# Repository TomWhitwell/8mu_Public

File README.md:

### 8mu Public Repo

This is the public repo for the Music Thing Modular 8mu midi controller. 

[Documentation is here](https://www.musicthing.co.uk/8mu)

Currently this contains firmware for 8mu v1, devices bought before August 2026 that have a SAMD21 chip. 

Devices bought after August 2026 are v2. They have v2 clearly marked next to the USB socket, and have a RP2040 chip. 
 
The current production SAMD21 8mu v1 firmware source is in
[`Firmware_v1/8mu`](Firmware_v1/8mu). Release firmware can be downloaded from the
[Smith-Kakehashi releases page](https://github.com/TomWhitwell/Smith-Kakehashi/releases).

This repo also contains source for the [legacy 8mu editor](https://tomwhitwell.github.io/Smith-Kakehashi/), which has now been replaced by the [main 16n Editor for 16m | 16nx | 8mu](https://16n-faderbank.github.io/editor/). 

Firmware is MIT Licensed. 
Hardware is CC-BY-SA.

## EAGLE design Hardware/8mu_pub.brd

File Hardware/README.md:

Open hardware files coming soon

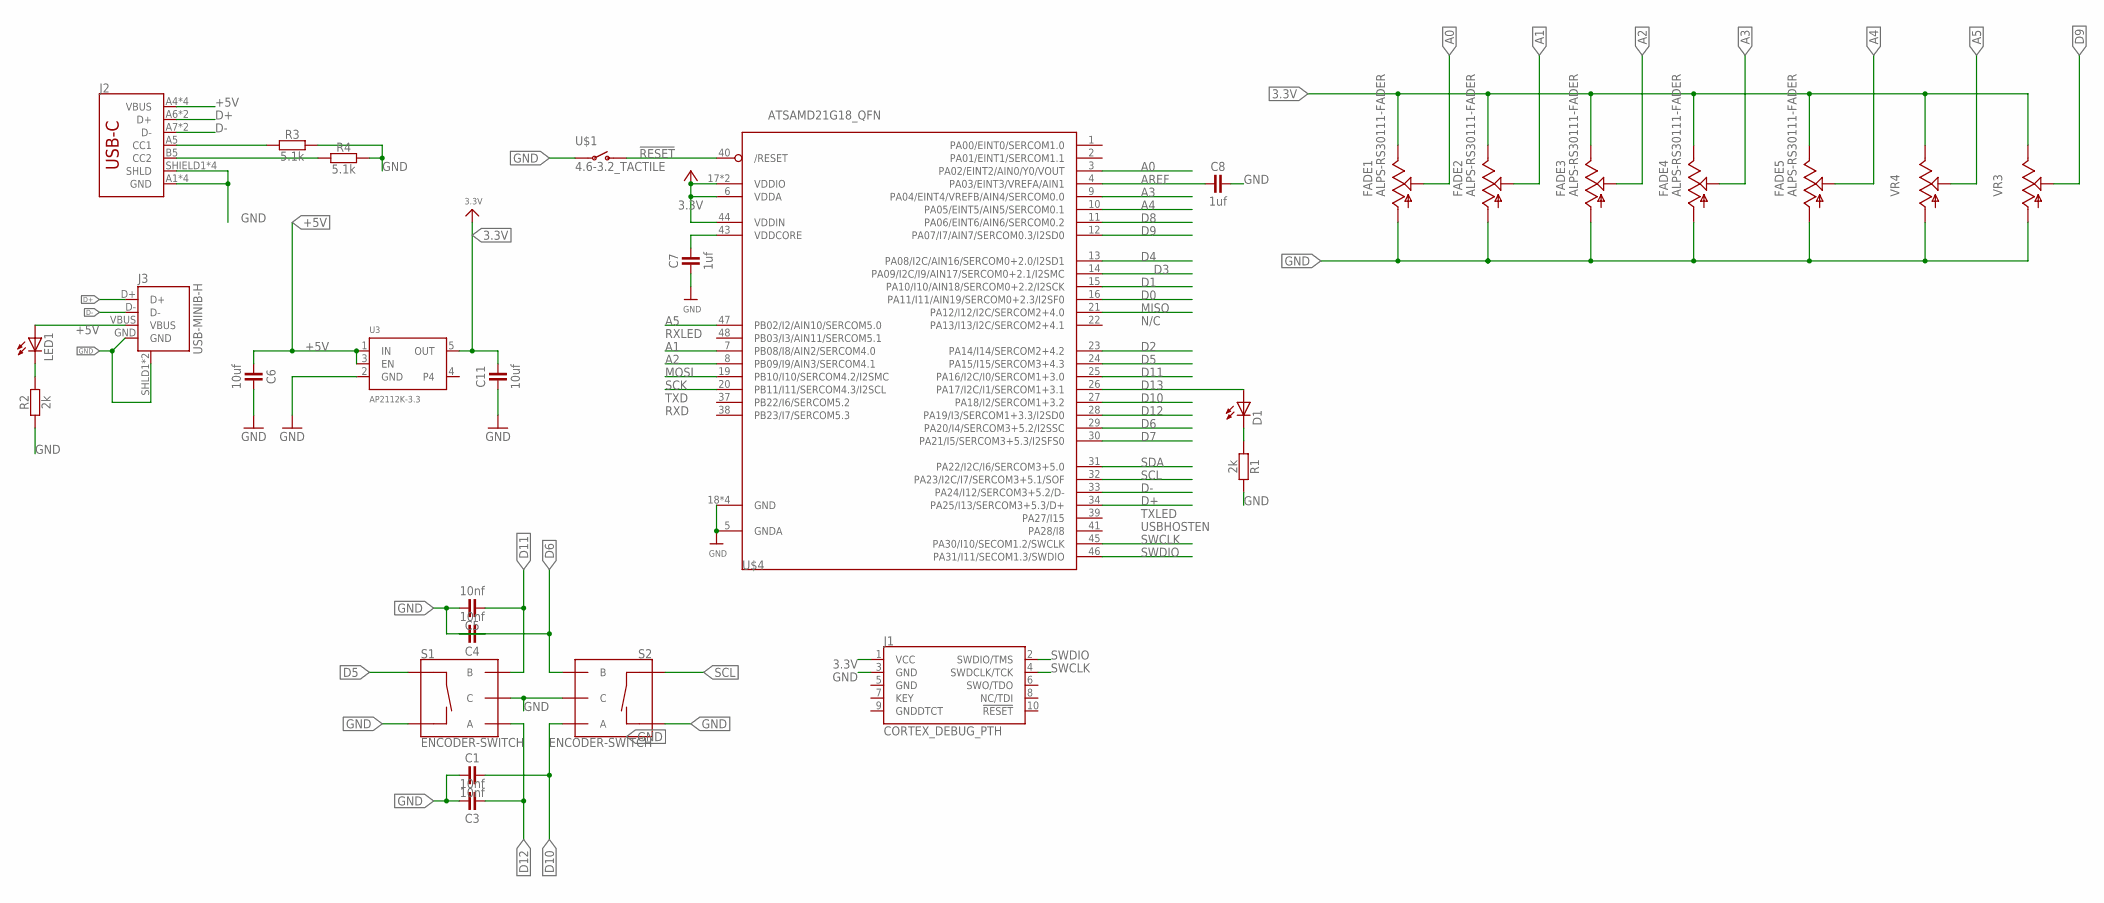
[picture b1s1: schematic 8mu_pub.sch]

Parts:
C1, C3, C4, C5: 10nf; C0603
C6, C11: 10uf; C0603
C7, C8: 1uf; C0603
D1: LED3MM
FADE1, FADE2, FADE3, FADE4, FADE5: ALPS-RS30111-FADER
J1: CORTEX_DEBUG_PTH; 2X5-PTH-1.27MM
J2: USB_C; CX90M-16P-USB-C-MIDMOUNT
J3: USB-MINIB-H
LED1: LED3MM
R1, R2: 2k; C0603
R3, R4: 5.1k; C0603
S1, S2: ENCODER-SWITCH; ROTARY_ENC_PLAIN
U3: AP2112K-3.3; SOT23-5
U$1: 4.6-3.2_TACTILE; TACTILE_SWITCH_SMD_4.6X2.8MM
U$4: ATSAMD21G18_QFN; TQFN48_7MM
VR3, VR4: 9MM_SNAP-IN_POT_; 9MM_SNAP-IN_POT

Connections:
3.3V: C11.2, FADE1.3 (E), FADE2.3 (E), FADE3.3 (E), FADE4.3 (E), FADE5.3 (E), J1.1 (VCC), U3.5 (OUT), U$4.6 (VDDA), U$4.17 (VDDIO), U$4.36 (VDDIO), U$4.44 (VDDIN), VR3.3 (E), VR4.3 (E)
!RESET: U$1.3 (O), U$1.4 (O), U$4.40 (/RESET)
+5V: C6.1, J2.A4 (VBUS), J2.A9 (VBUS), J2.B4 (VBUS), J2.B9 (VBUS), J3.VBUS, LED1.A, U3.1 (IN), U3.3 (EN)
A0: FADE1.2 (S), U$4.3 (PA02/EINT2/AIN0/Y0/VOUT)
A1: FADE2.2 (S), U$4.7 (PB08/I8/AIN2/SERCOM4.0)
A2: FADE3.2 (S), U$4.8 (PB09/I9/AIN3/SERCOM4.1)
A3: FADE4.2 (S), U$4.9 (PA04/EINT4/VREFB/AIN4/SERCOM0.0)
A4: FADE5.2 (S), U$4.10 (PA05/EINT5/AIN5/SERCOM0.1)
A5: U$4.47 (PB02/I2/AIN10/SERCOM5.0), VR4.2 (S)
AREF: C8.1, U$4.4 (PA03/EINT3/VREFA/AIN1)
D0: U$4.16 (PA11/I11/AIN19/SERCOM0+2.3/I2SF0)
D1: U$4.15 (PA10/I10/AIN18/SERCOM0+2.2/I2SCK)
D2: U$4.23 (PA14/I14/SERCOM2+4.2)
D3: U$4.14 (PA09/I2C/I9/AIN17/SERCOM0+2.1/I2SMC)
D4: U$4.13 (PA08/I2C/AIN16/SERCOM0+2.0/I2SD1)
D5: S1.SW+, U$4.24 (PA15/I15/SERCOM3+4.3)
D6: C4.2, S2.B, U$4.29 (PA20/I4/SERCOM3+5.2/I2SSC)
D7: U$4.30 (PA21/I5/SERCOM3+5.3/I2SFS0)
D8: U$4.11 (PA06/EINT6/AIN6/SERCOM0.2)
D9: U$4.12 (PA07/I7/AIN7/SERCOM0.3/I2SD0), VR3.2 (S)
D10: C1.2, S2.A, U$4.27 (PA18/I2/SERCOM1+3.2)
D11: C5.1, S1.B, U$4.25 (PA16/I2C/I0/SERCOM1+3.0)
D12: C3.1, S1.A, U$4.28 (PA19/I3/SERCOM1+3.3/I2SD0)
D13: D1.A, U$4.26 (PA17/I2C/I1/SERCOM1+3.1)
D+: J2.A6 (D+), J2.B6 (D+), J3.D+, U$4.34 (PA25/I13/SERCOM3+5.3/D+)
D-: J2.A7 (D-), J2.B7 (D-), J3.D-, U$4.33 (PA24/I12/SERCOM3+5.2/D-)
GND: C1.1, C3.2, C4.1, C5.2, C6.2, C7.1, C8.2, C11.1, FADE1.1 (A), FADE2.1 (A), FADE3.1 (A), FADE4.1 (A), FADE5.1 (A), J1.3 (GND), J2.A1 (GND), J2.A12 (GND), J2.B1 (GND), J2.B12 (GND), J2.SHIELD1 (SHLD), J2.SHIELD2 (SHLD), J2.SHIELD3 (SHLD), J2.SHIELD4 (SHLD), J3.GND, J3.SHLD1 (SHIELD), J3.SHLD2 (SHIELD), R1.2, R2.1, R3.2, R4.2, S1.C, S1.SW-, S2.C, S2.SW-, U3.2 (GND), U$1.1, U$1.2, U$4.5 (GNDA), U$4.18 (GND), U$4.35 (GND), U$4.42 (GND), U$4.THERMAL (GND), VR3.1 (A), VR4.1 (A)
MISO: U$4.21 (PA12/I12/I2C/SERCOM2+4.0)
MOSI: U$4.19 (PB10/I10/SERCOM4.2/I2SMC)
unnamed: D1.K (C), R1.1
unnamed: LED1.K (C), R2.2
unnamed: J2.A5 (CC1), R3.1
unnamed: J2.B5 (CC2), R4.1
SCK: U$4.20 (PB11/I11/SERCOM4.3/I2SCL)
SCL: S2.SW+, U$4.32 (PA23/I2C/I7/SERCOM3+5.1/SOF)
SDA: U$4.31 (PA22/I2C/I6/SERCOM3+5.0)
SWCLK: J1.4 (SWDCLK/TCK), U$4.45 (PA30/I10/SECOM1.2/SWCLK)
SWDIO: J1.2 (SWDIO/TMS), U$4.46 (PA31/I11/SECOM1.3/SWDIO)
VDDCORE: C7.2, U$4.43 (VDDCORE)

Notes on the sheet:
N/C
TXLED
USBHOSTEN
RXLED
TXD
RXD

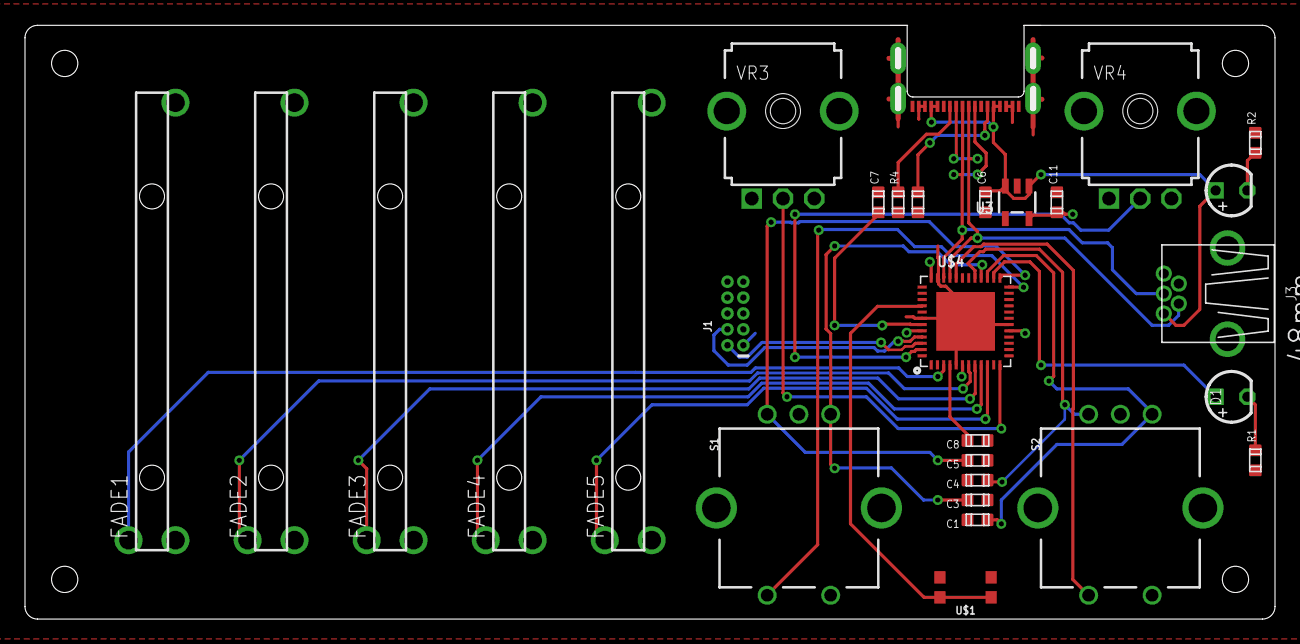
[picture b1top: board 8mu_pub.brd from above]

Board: 2 copper layers, 99.5 x 47.0 mm, 29 parts (0 on the bottom side), 28 nets.

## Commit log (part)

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2022-12-14 License and readme
2022-12-14 initial files
2023-03-07 Remove placeholder files
2023-03-27 upload hello world files
2023-04-03 Pre-launch upload
2023-04-06 SK2: Add 16n mk2 editor.
2023-04-06 Latest version of SvelteKit.
2023-04-16 Version for the beta testers
2023-04-18 Bump package versions.
2023-04-18 Types now reflect 8mu configuration.
2023-04-18 Add some TW copy.
2023-04-18 Bring configuration library up to 8mu spec.
2023-04-18 Remove factory reset functionality (not on 8mu)
2023-04-18 Update MIDI library to reflect 8u editor changes.
2023-04-18 Go over all components.
2023-04-18 Update device options.
2023-04-18 Update viewing mode, and add tips library.
2023-04-18 Completing first pass of mk2 editor.
2023-04-18 Update package.json.
2023-04-18 Formatting + Linting.
2023-04-18 Produce nicer export filenames.
2023-04-18 8MU favicon.
2023-04-18 Fix link to release downloads.
2023-04-18 Rename directory.
2023-04-18 Fettle README.
2023-04-18 Fixup reference to 16n.
2023-04-19 Update instruction.
2023-04-19 Format churn.
2023-04-23 fixes #2
2023-04-23 v1.0.2 Fixes #1 and improves smoothing of fader channels and more aggressive smoothing on IMU channels
2023-04-24 Ignore debug netlify config.
2023-04-24 New 2.0.0 Editor is now the only editor.
2023-04-24 Remove code linting workflow from 8mu editor.
2023-04-29 Remove TA's old TODO list from the Editor.
2023-04-30 fix tips and unicode spin left / right in editor, remove todo
2023-05-02 styling for upgrade + footer link to old version
2023-05-08 v1.0.2 firmware code fixes #8 fixes #2 fixes #1

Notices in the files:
parts and their libraries:
microbuilder: This work is placed in the public domain, and may be freely used for commercial and non-commercial work with the following conditions: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
SparkFun-Switches: Licensing: Creative Commons ShareAlike 4.0 International - https://creativecommons.org/licenses/by-sa/4.0
